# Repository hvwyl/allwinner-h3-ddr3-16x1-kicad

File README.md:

# allwinner-h3-ddr3-16x1-kicad
Allwinner H3 with ddr3 16x1 design reference  for KiCad

## Schematic

## PCB Layout

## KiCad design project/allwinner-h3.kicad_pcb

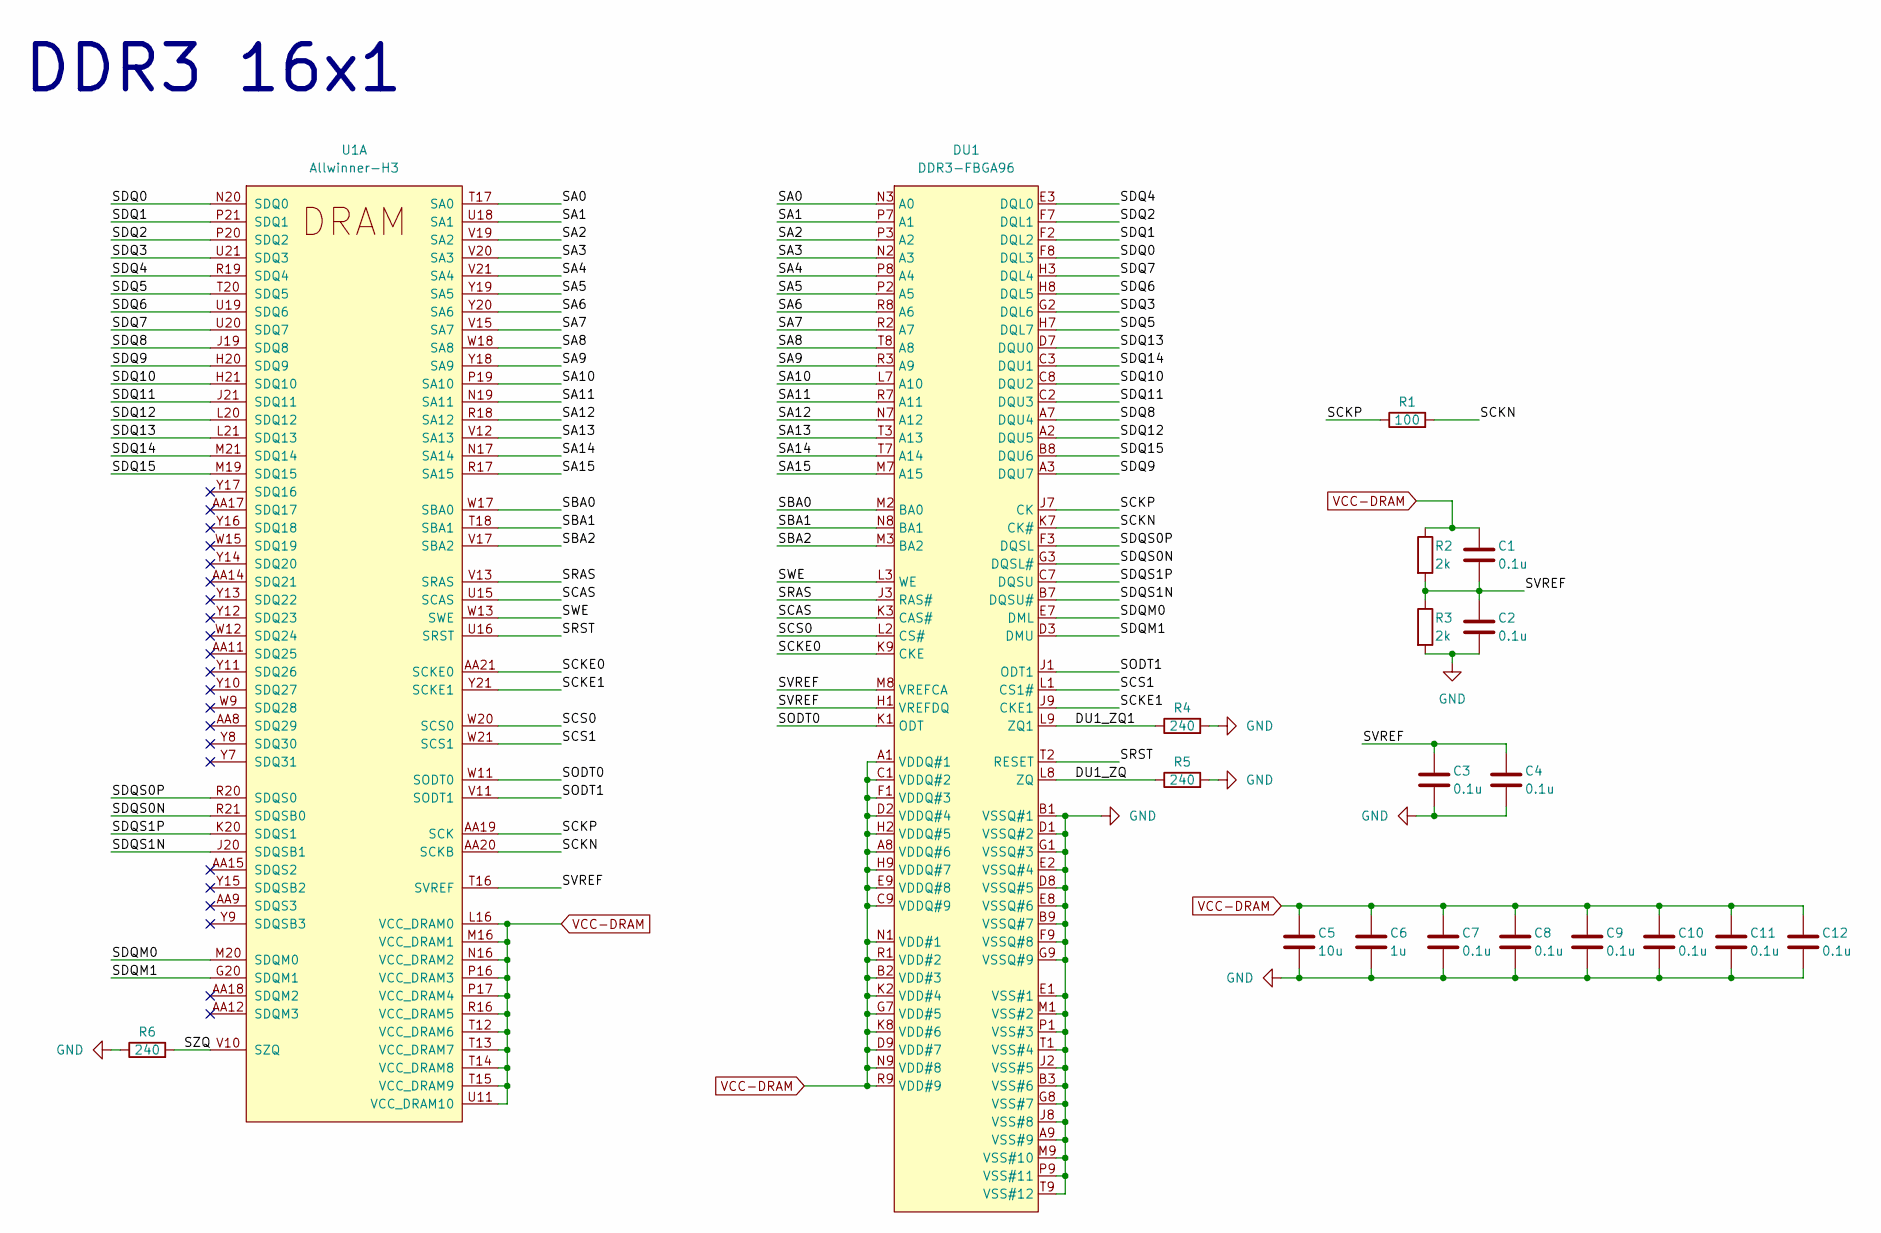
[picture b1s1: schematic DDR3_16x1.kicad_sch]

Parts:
C1, C2, C3, C4, C7, C8, C9, C10, C11, C12: 0.1u; C_0402_1005Metric
C5: 10u; C_0402_1005Metric
C6: 1u; C_0402_1005Metric
DU1: DDR3-FBGA96; Micron_FBGA-96_8x14mm_Layout9x16_P0.8mm
R1: 100; R_0402_1005Metric
R2, R3: 2k; R_0402_1005Metric
R4, R5, R6: 240; R_0402_1005Metric
U1: Allwinner-H3

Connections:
/DDR3 16x1/DU1_ZQ: DU1.L8 (ZQ), R5.1
/DDR3 16x1/DU1_ZQ1: DU1.L9 (ZQ1), R4.1
/DDR3 16x1/SA0: DU1.N3 (A0), U1.T17 (SA0)
/DDR3 16x1/SA1: DU1.P7 (A1), U1.U18 (SA1)
/DDR3 16x1/SA2: DU1.P3 (A2), U1.V19 (SA2)
/DDR3 16x1/SA3: DU1.N2 (A3), U1.V20 (SA3)
/DDR3 16x1/SA4: DU1.P8 (A4), U1.V21 (SA4)
/DDR3 16x1/SA5: DU1.P2 (A5), U1.Y19 (SA5)
/DDR3 16x1/SA6: DU1.R8 (A6), U1.Y20 (SA6)
/DDR3 16x1/SA7: DU1.R2 (A7), U1.V15 (SA7)
/DDR3 16x1/SA8: DU1.T8 (A8), U1.W18 (SA8)
/DDR3 16x1/SA9: DU1.R3 (A9), U1.Y18 (SA9)
/DDR3 16x1/SA10: DU1.L7 (A10), U1.P19 (SA10)
/DDR3 16x1/SA11: DU1.R7 (A11), U1.N19 (SA11)
/DDR3 16x1/SA12: DU1.N7 (A12), U1.R18 (SA12)
/DDR3 16x1/SA13: DU1.T3 (A13), U1.V12 (SA13)
/DDR3 16x1/SA14: DU1.T7 (A14), U1.N17 (SA14)
/DDR3 16x1/SA15: DU1.M7 (A15), U1.R17 (SA15)
/DDR3 16x1/SBA0: DU1.M2 (BA0), U1.W17 (SBA0)
/DDR3 16x1/SBA1: DU1.N8 (BA1), U1.T18 (SBA1)
/DDR3 16x1/SBA2: DU1.M3 (BA2), U1.V17 (SBA2)
/DDR3 16x1/SCAS: DU1.K3 (CAS#), U1.U15 (SCAS)
/DDR3 16x1/SCKE0: DU1.K9 (CKE), U1.AA21 (SCKE0)
/DDR3 16x1/SCKE1: DU1.J9 (CKE1), U1.Y21 (SCKE1)
/DDR3 16x1/SCKN: DU1.K7 (CK#), R1.2, U1.AA20 (SCKB)
/DDR3 16x1/SCKP: DU1.J7 (CK), R1.1, U1.AA19 (SCK)
/DDR3 16x1/SCS0: DU1.L2 (CS#), U1.W20 (SCS0)
/DDR3 16x1/SCS1: DU1.L1 (CS1#), U1.W21 (SCS1)
/DDR3 16x1/SDQ0: DU1.F8 (DQL3), U1.N20 (SDQ0)
/DDR3 16x1/SDQ1: DU1.F2 (DQL2), U1.P21 (SDQ1)
/DDR3 16x1/SDQ2: DU1.F7 (DQL1), U1.P20 (SDQ2)
/DDR3 16x1/SDQ3: DU1.G2 (DQL6), U1.U21 (SDQ3)
/DDR3 16x1/SDQ4: DU1.E3 (DQL0), U1.R19 (SDQ4)
/DDR3 16x1/SDQ5: DU1.H7 (DQL7), U1.T20 (SDQ5)
/DDR3 16x1/SDQ6: DU1.H8 (DQL5), U1.U19 (SDQ6)
/DDR3 16x1/SDQ7: DU1.H3 (DQL4), U1.U20 (SDQ7)
/DDR3 16x1/SDQ8: DU1.A7 (DQU4), U1.J19 (SDQ8)
/DDR3 16x1/SDQ9: DU1.A3 (DQU7), U1.H20 (SDQ9)
/DDR3 16x1/SDQ10: DU1.C8 (DQU2), U1.H21 (SDQ10)
/DDR3 16x1/SDQ11: DU1.C2 (DQU3), U1.J21 (SDQ11)
/DDR3 16x1/SDQ12: DU1.A2 (DQU5), U1.L20 (SDQ12)
/DDR3 16x1/SDQ13: DU1.D7 (DQU0), U1.L21 (SDQ13)
/DDR3 16x1/SDQ14: DU1.C3 (DQU1), U1.M21 (SDQ14)
/DDR3 16x1/SDQ15: DU1.B8 (DQU6), U1.M19 (SDQ15)
/DDR3 16x1/SDQM0: DU1.E7 (DML), U1.M20 (SDQM0)
/DDR3 16x1/SDQM1: DU1.D3 (DMU), U1.G20 (SDQM1)
/DDR3 16x1/SDQS0N: DU1.G3 (DQSL#), U1.R21 (SDQSB0)
/DDR3 16x1/SDQS0P: DU1.F3 (DQSL), U1.R20 (SDQS0)
/DDR3 16x1/SDQS1N: DU1.B7 (DQSU#), U1.J20 (SDQSB1)
/DDR3 16x1/SDQS1P: DU1.C7 (DQSU), U1.K20 (SDQS1)
/DDR3 16x1/SODT0: DU1.K1 (ODT), U1.W11 (SODT0)
/DDR3 16x1/SODT1: DU1.J1 (ODT1), U1.V11 (SODT1)
/DDR3 16x1/SRAS: DU1.J3 (RAS#), U1.V13 (SRAS)
/DDR3 16x1/SRST: DU1.T2 (RESET), U1.U16 (SRST)
/DDR3 16x1/SVREF: C1.2, C2.1, C3.1, C4.1, DU1.H1 (VREFDQ), DU1.M8 (VREFCA), R2.2, R3.1, U1.T16 (SVREF)
/DDR3 16x1/SWE: DU1.L3 (WE), U1.W13 (SWE)
/DDR3 16x1/SZQ: R6.2, U1.V10 (SZQ)
GND: C2.2, C3.2, C4.2, C5.2, C6.2, C7.2, C8.2, C9.2, C10.2, C11.2, C12.2, DU1.A9 (VSS#9), DU1.B1 (VSSQ#1), DU1.B3 (VSS#6), DU1.B9 (VSSQ#7), DU1.D1 (VSSQ#2), DU1.D8 (VSSQ#5), DU1.E1 (VSS#1), DU1.E2 (VSSQ#4), DU1.E8 (VSSQ#6), DU1.F9 (VSSQ#8), DU1.G1 (VSSQ#3), DU1.G8 (VSS#7), DU1.G9 (VSSQ#9), DU1.J2 (VSS#5), DU1.J8 (VSS#8), DU1.M1 (VSS#2), DU1.M9 (VSS#10), DU1.P1 (VSS#3), DU1.P9 (VSS#11), DU1.T1 (VSS#4), DU1.T9 (VSS#12), R3.2, R4.2, R5.2, R6.1
VCC-DRAM: C1.1, C5.1, C6.1, C7.1, C8.1, C9.1, C10.1, C11.1, C12.1, DU1.A1 (VDDQ#1), DU1.A8 (VDDQ#6), DU1.B2 (VDD#3), DU1.C1 (VDDQ#2), DU1.C9 (VDDQ#9), DU1.D2 (VDDQ#4), DU1.D9 (VDD#7), DU1.E9 (VDDQ#8), DU1.F1 (VDDQ#3), DU1.G7 (VDD#5), DU1.H2 (VDDQ#5), DU1.H9 (VDDQ#7), DU1.K2 (VDD#4), DU1.K8 (VDD#6), DU1.N1 (VDD#1), DU1.N9 (VDD#8), DU1.R1 (VDD#2), DU1.R9 (VDD#9), R2.1, U1.L16 (VCC_DRAM0), U1.M16 (VCC_DRAM1), U1.N16 (VCC_DRAM2), U1.P16 (VCC_DRAM3), U1.P17 (VCC_DRAM4), U1.R16 (VCC_DRAM5), U1.T12 (VCC_DRAM6), U1.T13 (VCC_DRAM7), U1.T14 (VCC_DRAM8), U1.T15 (VCC_DRAM9), U1.U11 (VCC_DRAM10)

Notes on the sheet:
DDR3 16x1

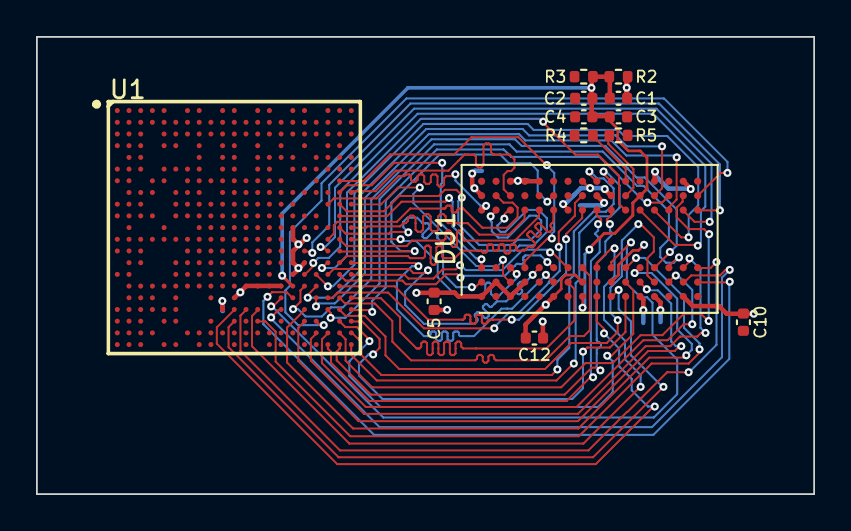
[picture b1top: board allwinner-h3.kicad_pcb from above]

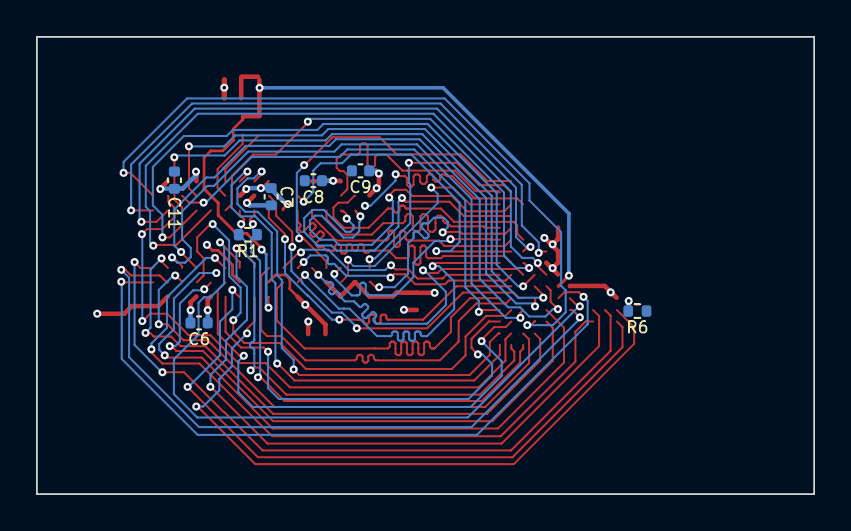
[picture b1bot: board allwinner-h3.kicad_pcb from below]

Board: 2 copper layers, 43.2 x 25.4 mm, 20 parts (7 on the bottom side), 59 nets.

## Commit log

2023-08-30 version 1.0.0
